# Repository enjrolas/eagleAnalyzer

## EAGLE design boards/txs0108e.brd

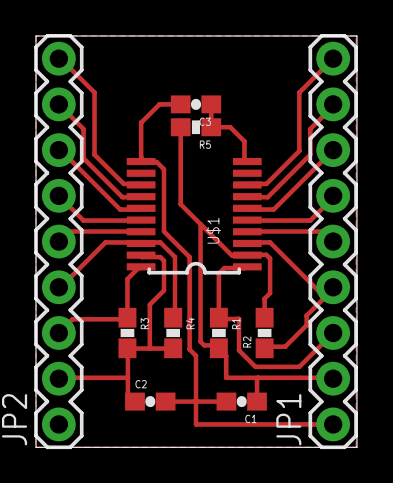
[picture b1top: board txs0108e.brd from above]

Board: 2 copper layers, 17.8 x 22.9 mm, 11 parts (0 on the bottom side), 18 nets.

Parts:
C1, C2, C3: 1uF; 0603-CAP
JP1, JP2: M09; 1X09
R1, R2, R3, R4: 4k7; 0603-RES
R5: 10k; 0603-RES
U$1: TXS0108E; TSSOP20

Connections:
3.3V: C1.1, JP1.2, R1.2, R2.2, R5.2, U$1.2
5V: C2.1, JP2.2, R3.2, R4.2, U$1.19
A1: JP1.3, R1.1, U$1.1
A2: JP1.4, R2.1, U$1.3
A3: JP1.5, U$1.4
A4: JP1.6, U$1.5
A5: JP1.7, U$1.6
A6: JP1.8, U$1.7
A7: JP1.9, U$1.8
B1: JP2.3, R3.1, U$1.20
B2: JP2.4, R4.1, U$1.18
B3: JP2.5, U$1.17
B4: JP2.6, U$1.16
B5: JP2.7, U$1.15
B6: JP2.8, U$1.14
B7: JP2.9, U$1.13
GND: C1.2, C2.2, C3.2, JP1.1, U$1.11
OE: C3.1, R5.1, U$1.10

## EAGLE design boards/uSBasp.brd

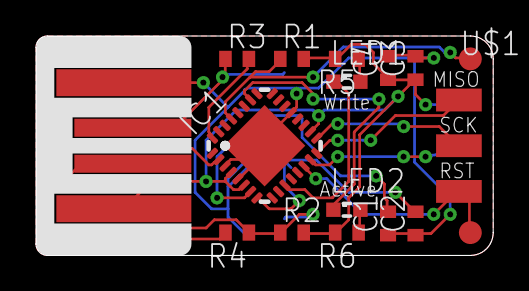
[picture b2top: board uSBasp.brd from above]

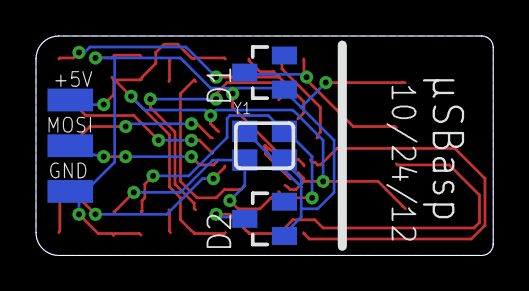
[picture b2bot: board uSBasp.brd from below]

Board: 2 copper layers, 25.4 x 12.2 mm, 20 parts (3 on the bottom side), 17 nets.

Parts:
C1, C2: 22pF; C0402
C3: 0.1uF; C0402
C4: 4.7uF; C0402
D1, D2: 3V6; SOT23
IC1: MEGA8-MI; MLF32-TH
LED1: Write (R); SML0603
LED2: Active (G); SML0603
R1: 10k; R0402
R2: 2.2k; R0402
R3, R4: 68; R0402
R5, R6: 1k; R0402
TP1, TP2: TEST-POINT3X5; PAD.03X.05
U$1: M-2X03PTH; M-2X03-0.1-PTH-EDGE
X1: USBPCB; USB-A-PCB
Y1: 12Mhz; CRYSTAL-SMD-3.2X2.5

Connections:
+5V: C3.1, C4.1, IC1.4, IC1.6, IC1.18, R1.2, R2.2, R5.2, R6.2, U$1.2, X1.5V
D+: IC1.32, R3.2
D-: IC1.2, R4.2
GND: C1.1, C2.1, C3.2, C4.2, D1.1, D2.1, IC1.3, IC1.5, IC1.21, IC1.TH, U$1.6, X1.GND, Y1.2, Y1.4
LED-A: IC1.26, LED2.C
LED-W: IC1.11, LED1.C
MISO: IC1.16, U$1.1
MOSI: IC1.15, U$1.4
unnamed: LED1.A, R5.1
unnamed: LED2.A, R6.1
unnamed: D1.3, R3.1, X1.USB_P
unnamed: D2.3, R2.1, R4.1, X1.USB_M
unnamed: C1.2, IC1.7, Y1.3
unnamed: C2.2, IC1.8, Y1.1
RESET: IC1.14, TP2.P$1, U$1.5
SCK: IC1.17, U$1.3
SELFPROG: IC1.29, R1.1, TP1.P$1

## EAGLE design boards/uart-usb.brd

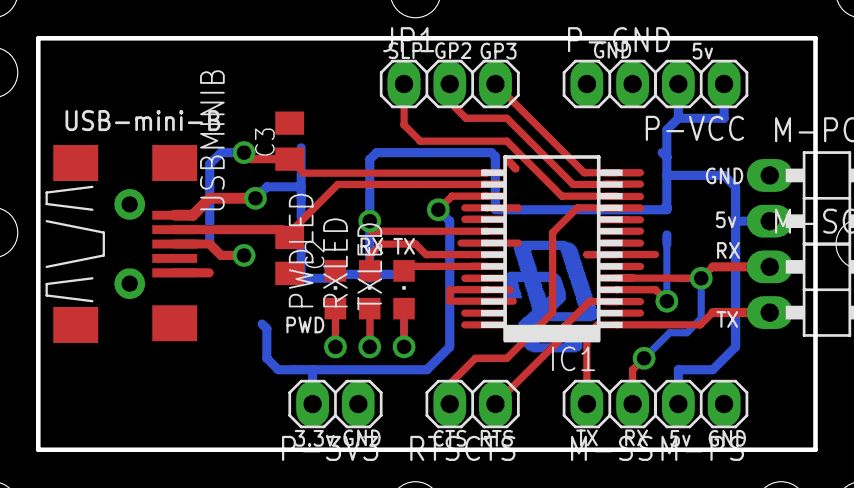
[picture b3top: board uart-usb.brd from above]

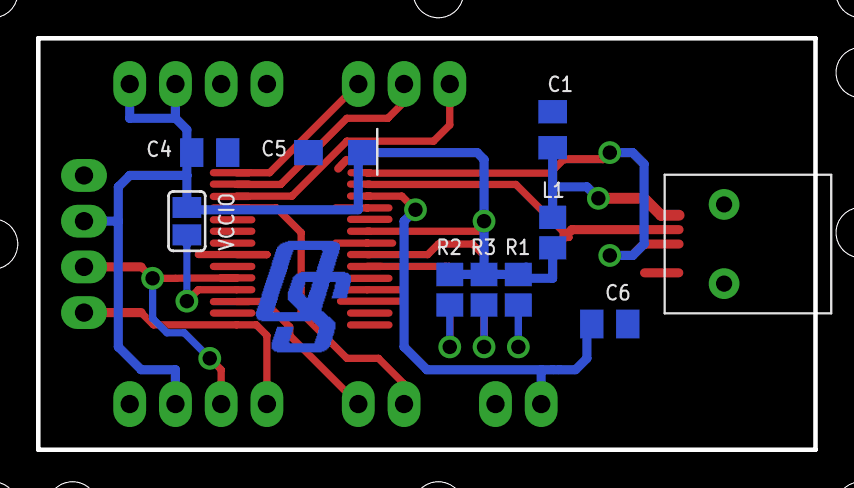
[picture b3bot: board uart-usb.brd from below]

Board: 2 copper layers, 43.2 x 22.9 mm, 27 parts (10 on the bottom side), 19 nets.

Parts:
C1: 10nF**; C0805K
C2, C3: 47pF**; C0805K
C4: 100nF; C0805K
C5: 4.7uF 20V; SMC_A
C6: 100n; C0805K
DRILEGEND: DRILEGEND
IC1: FT232RL; SSOP-28
JP1: 1X03
L1: 0 H; R0805
M-PC: 1X02/90
M-PS: 1X02
M-SC: 1X02/90
M-SS: 1X02
P-3V3: 1X02
P-GND: 1X02
P-VCC: 1X02
PWDLED: CHIPLED_0805
R1, R2: 270; R0805
R3: 510; R0805
RTSCTS: 1X02
RXLED: CHIPLED_0805
TXLED: CHIPLED_0805
U$1: SMP_OS12
USBMINIB: USB-MB-S
VCCIO: SJ

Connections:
3V3OUT: C6.1, IC1.17, P-3V3.2
CTS: IC1.11, RTSCTS.2
D+: C3.1, IC1.15, USBMINIB.D+
D-: C2.1, IC1.16, USBMINIB.D-
GND: C1.2, C2.2, C3.2, C4.2, C5.-, C6.2, IC1.7, IC1.18, IC1.21, IC1.25, IC1.26, M-PC.1, M-PS.1, P-3V3.1, P-GND.1, P-GND.2, PWDLED.C, USBMINIB.GND
GPIO2: IC1.13, JP1.2
GPIO3: IC1.14, JP1.3
unnamed: R3.2, RXLED.A
unnamed: PWDLED.A, R1.2
unnamed: R2.2, TXLED.A
unnamed: C1.1, L1.1, USBMINIB.VBUS
RTS: IC1.3, RTSCTS.1
RXD: IC1.5, M-SC.1, M-SS.1
RXLED: IC1.22, RXLED.C
SLEEP: IC1.12, JP1.1
TXD: IC1.1, M-SC.2, M-SS.2
TXLED: IC1.23, TXLED.C
VCC: C4.1, C5.+, IC1.20, L1.2, M-PC.2, M-PS.2, P-VCC.1, P-VCC.2, R1.1, R2.1, R3.1, VCCIO.1
VCCIO: IC1.4, VCCIO.2

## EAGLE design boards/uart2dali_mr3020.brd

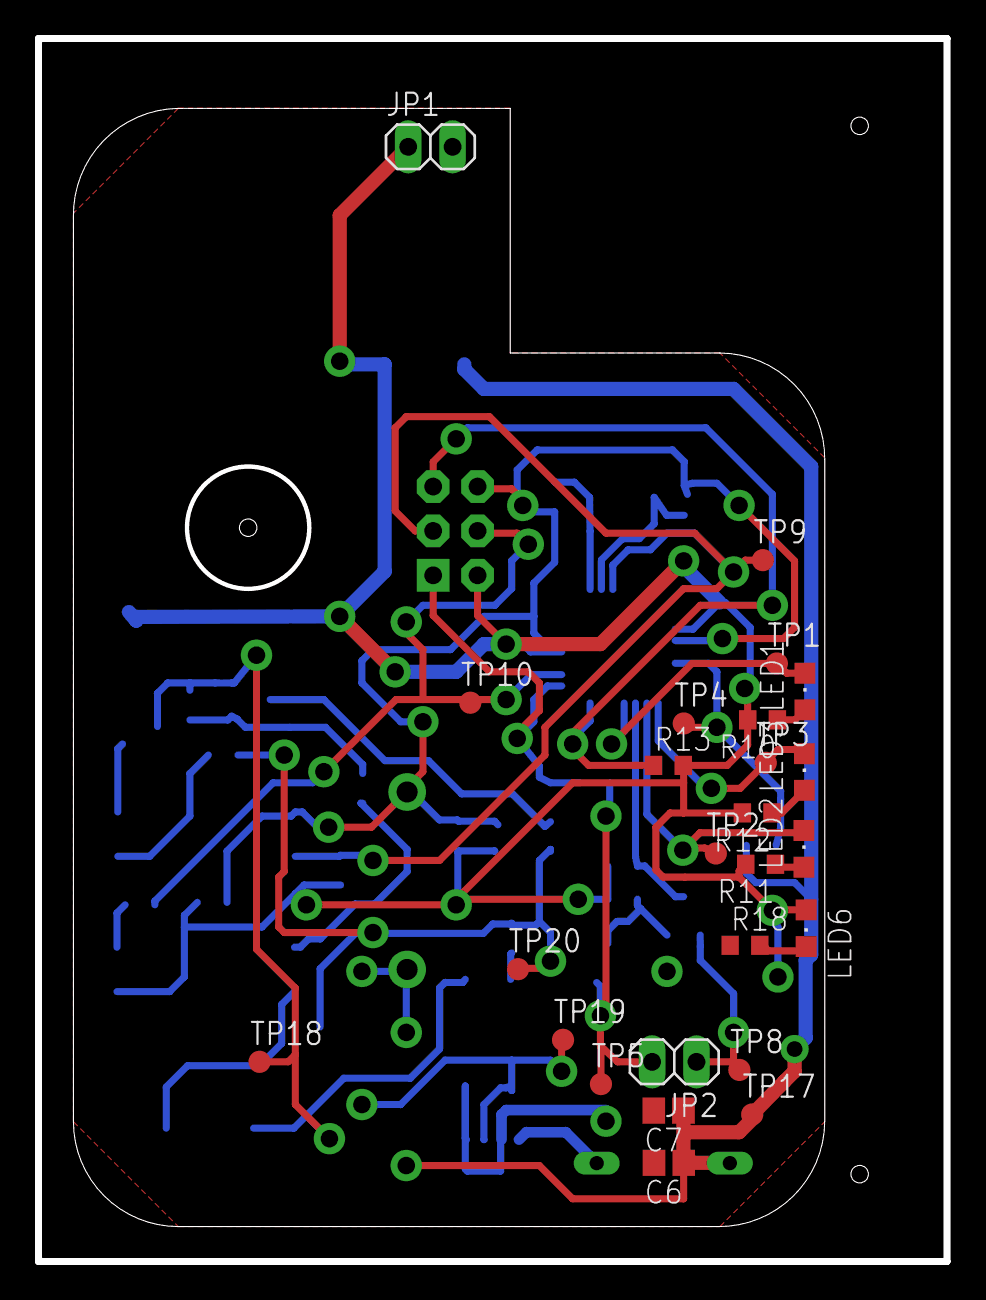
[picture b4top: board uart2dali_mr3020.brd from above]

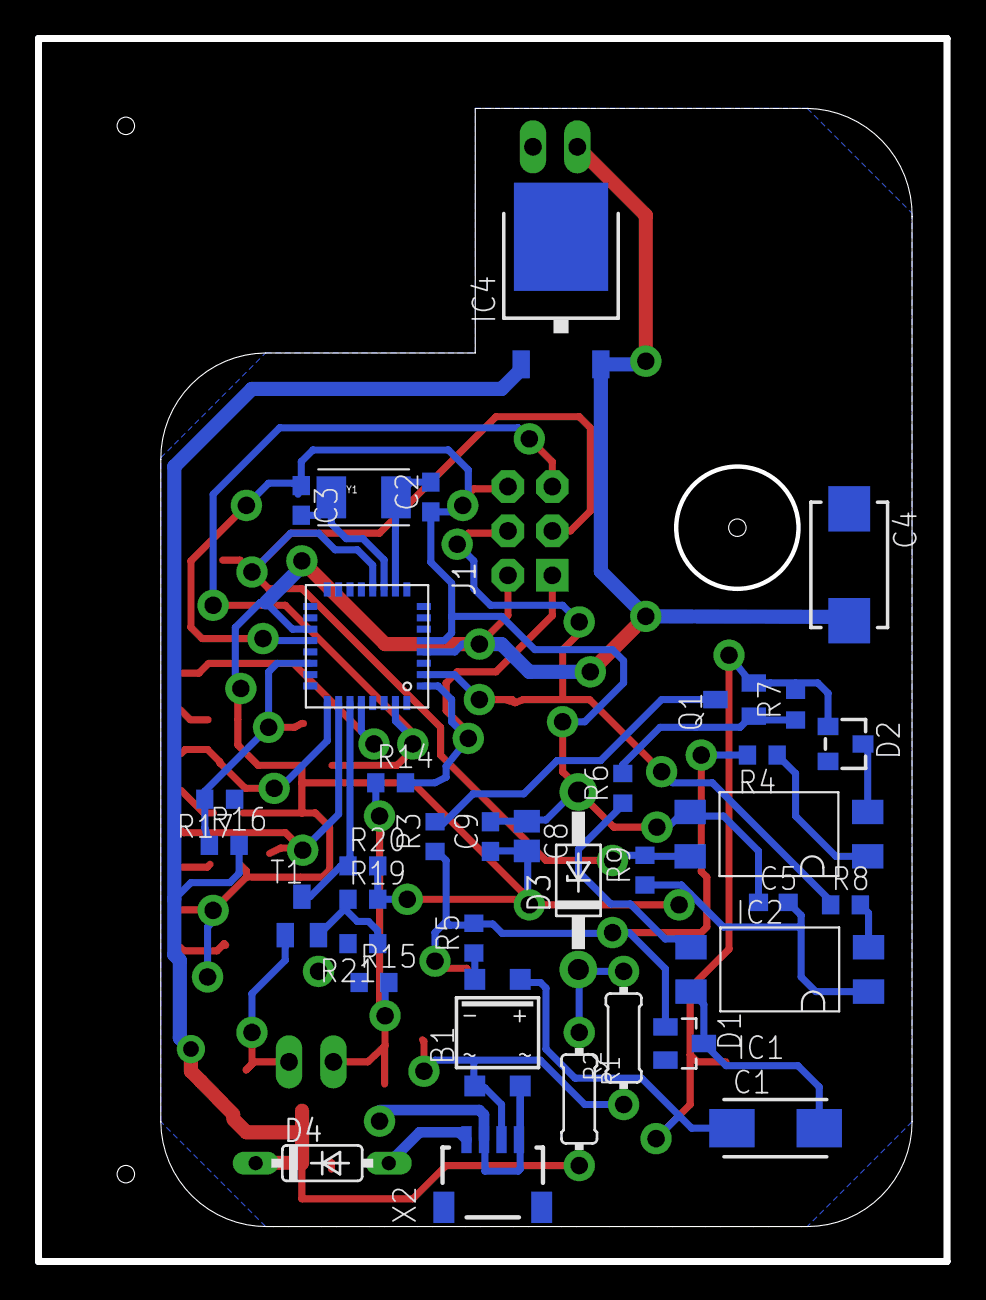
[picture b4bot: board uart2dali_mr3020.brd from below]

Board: 2 copper layers, 52.0 x 70.0 mm, 62 parts (37 on the bottom side), 34 nets.

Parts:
B1: MB2S; SOIC-4
C1: CT6032
C2, C3, C5, C9: C0603
C4: CT7343
C6, C7, C8: C0805
D1: BAS40; SOT23
D2: BZX84CSMD; TO236
D3: BZX85; DO41Z10
D4: 1N4148DO35-7; DO35-7
IC1, IC2: SFH6156; SFH
IC4: 7805DT; TO252
J1: AVR_SPI_PRG_6NS; 2X3-NS
JP1, JP2: 1X02
LED1, LED2, LED3, LED6: CHIPLED_0805
Q1: BC817-25SMD; SOT23-BEC
R1, R2: 0204/7
R3, R4, R5, R6, R7, R8, R9, R10, R11, R12, R13, R14, R15, R16, R17, R18, R19, R20, R21: R0603
T1: SOT23-EBC
TP1, TP2, TP3, TP4, TP5, TP8, TP9, TP10, TP17, TP18, TP19, TP20: TPB1,27; B1,27
U$1: AT90PWM316; QFN32_7MM
X2: SM04B-SRSS-TB
Y1: CRYSTAL-TXC-7A

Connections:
+5V: C4.+, C5.2, C8.2, C9.1, IC1.1, IC4.2, J1.2, JP1.1, LED6.A, R9.1, R10.2, R11.2, R12.2, R13.2, R19.2, R20.2, U$1.P4, U$1.P19
DALI_RCV: IC2.4, J1.3, R9.2, TP9.TP, U$1.P12
DALI_TRM: J1.4, R8.1, TP10.TP, U$1.P2
GND: B1.~2, C2.1, C3.1, C4.-, C5.1, C6.2, C7.2, C8.1, C9.2, D3.A, IC2.3, IC4.3, J1.6, JP1.2, R15.1, R17.1, R18.1, R21.2, U$1.P5, U$1.P20, X2.2, X2.4
MISO: J1.1, R14.2, U$1.P1
unnamed: IC1.2, R8.2
unnamed: B1.~1, R2.1, TP19.TP, X2.3
unnamed: D3.C, R1.1, R2.2
unnamed: C1.+, D1.3, IC1.4
unnamed: IC1.3, R6.1
unnamed: Q1.B, R6.2, R7.1
unnamed: B1.+, C1.-, D2.A, Q1.E, R7.2, TP18.TP
unnamed: LED1.A, R10.1
unnamed: D1.1, R3.1, R4.2, R5.2, TP20.TP
unnamed: Q1.C, R3.2
unnamed: IC2.1, R4.1
unnamed: D2.C, IC2.2
unnamed: B1.-, R5.1
unnamed: LED2.A, R11.1
unnamed: LED3.A, R12.1
unnamed: C2.2, U$1.P10, Y1.P$1
unnamed: C3.2, U$1.P11, Y1.P$2
unnamed: R19.1, R21.1, T1.B
unnamed: R20.1, T1.C, U$1.P27
unnamed: D4.A, X2.1
unnamed: LED3.C, TP3.TP, U$1.P25
unnamed: LED2.C, TP2.TP, U$1.P26
unnamed: LED1.C, TP1.TP, U$1.P28
unnamed: R16.1, R17.2, TP4.TP, U$1.P22
unnamed: LED6.C, R18.2
RESET: J1.5, R13.1, U$1.P31
SOFT_RXD: JP2.1, T1.E, TP8.TP
SOFT_TXD: JP2.2, R14.1, R15.2, TP5.TP
VDD: C6.1, C7.1, D4.C, IC4.1, R1.2, R16.2, TP17.TP

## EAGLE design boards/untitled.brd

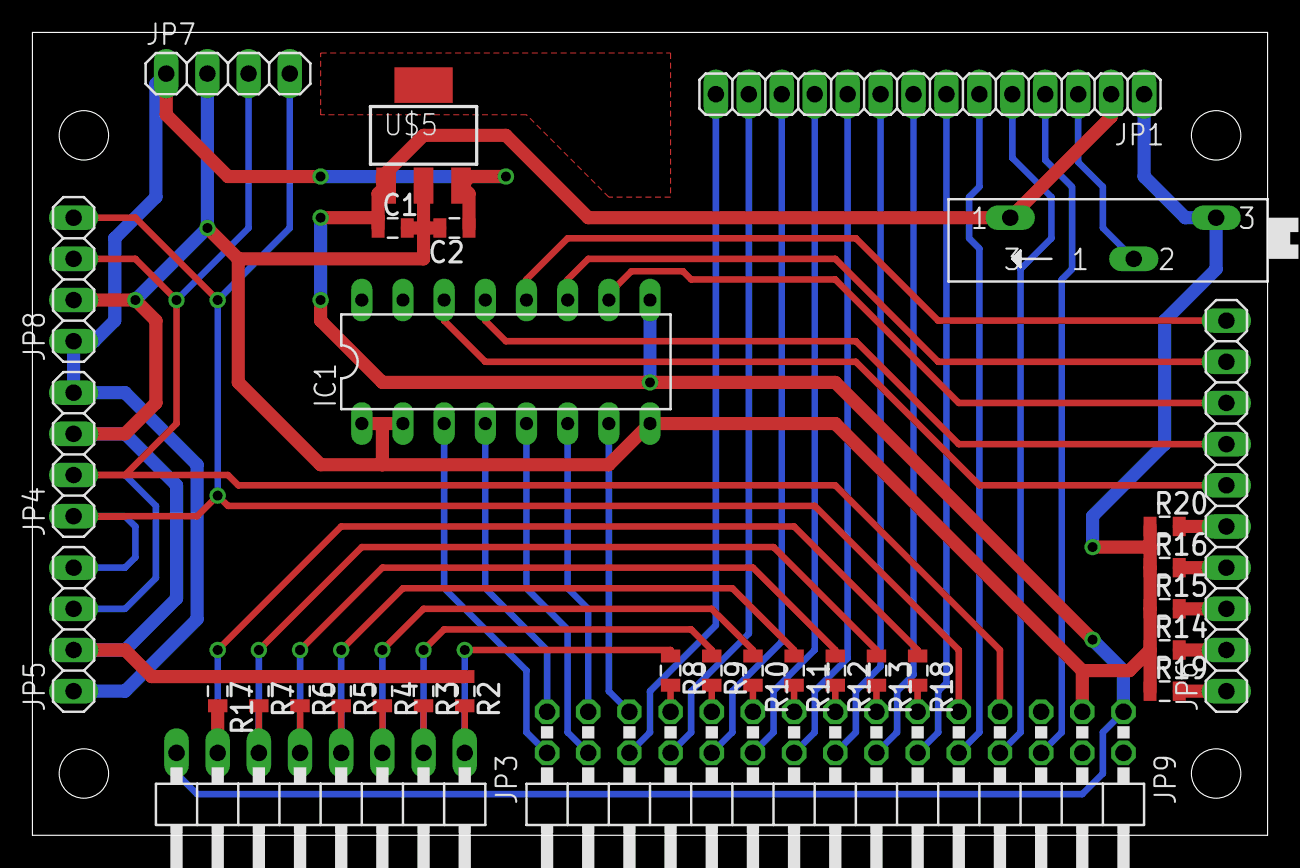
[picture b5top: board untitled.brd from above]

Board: 2 copper layers, 76.2 x 49.5 mm, 36 parts (0 on the bottom side), 46 nets.

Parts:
C1, C2: 0805
IC1: ULN2004AN; DIL16
JP1: 1X14
JP3: 1X08/90
JP4, JP5, JP7, JP8: 1X04
JP6: 1X10
JP9: 2X15/90
R1: SP19L
R2, R3, R4, R5, R6, R7, R8, R9, R10, R11, R12, R13, R14, R15, R16, R17, R18, R19, R20: 0805
U$1, U$2, U$3, U$4: STAND-OFF-TIGHT
U$5: LM3940IMP-3.3; SOT223

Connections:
3.3V: C2.1, JP4.4, JP5.1, JP7.1, JP8.1, U$5.3
GND: C1.2, C2.2, IC1.1, IC1.2, IC1.8, JP1.1, JP4.3, JP5.2, JP7.2, JP8.2, JP9.3, R1.E, R2.1, R3.1, R4.1, R5.1, R6.1, R7.1, R14.1, R15.1, R16.1, R17.1, R19.1, R20.1, U$5.2
unnamed: JP1.3, R1.S
unnamed: JP3.1, R2.2, R8.1
unnamed: JP3.2, R3.2, R9.1
unnamed: JP1.4, JP9.6
unnamed: JP1.5, JP9.8
unnamed: JP1.6, JP9.10
unnamed: JP1.7, JP9.12
unnamed: JP4.1, JP5.4, JP7.4, JP8.4, JP9.9
unnamed: JP1.8, JP9.14
unnamed: JP1.9, JP9.16
unnamed: JP1.10, JP9.18
unnamed: JP1.11, JP9.20
unnamed: JP1.12, JP9.22
unnamed: JP1.13, JP9.24
unnamed: JP3.3, R4.2, R10.1
unnamed: JP3.4, R5.2, R11.1
unnamed: JP3.5, R6.2, R12.1
unnamed: JP3.6, R7.2, R13.1
unnamed: JP9.13, R13.2
unnamed: JP9.15, R12.2
unnamed: JP9.17, R11.2
unnamed: JP9.19, R10.2
unnamed: JP9.21, R9.2
unnamed: JP9.23, R8.2
unnamed: JP1.14, JP9.26
unnamed: JP3.7, R17.2, R18.1
unnamed: IC1.7, JP9.25
unnamed: JP6.2, R14.2
unnamed: JP6.3, R15.2
unnamed: JP6.4, R16.2
unnamed: IC1.12, JP6.10
unnamed: IC1.5, JP9.28
unnamed: JP4.2, JP5.3, JP7.3, JP8.3, JP9.7
unnamed: JP9.11, R18.2
unnamed: JP6.1, R19.2
unnamed: JP6.5, R20.2
unnamed: IC1.4, JP9.29
unnamed: IC1.3, JP9.30
unnamed: IC1.10, JP6.8
unnamed: IC1.11, JP6.9
unnamed: IC1.13, JP6.7
unnamed: IC1.14, JP6.6
unnamed: IC1.6, JP9.27
VCC: C1.1, IC1.9, JP1.2, JP3.8, JP9.1, R1.A, U$5.1

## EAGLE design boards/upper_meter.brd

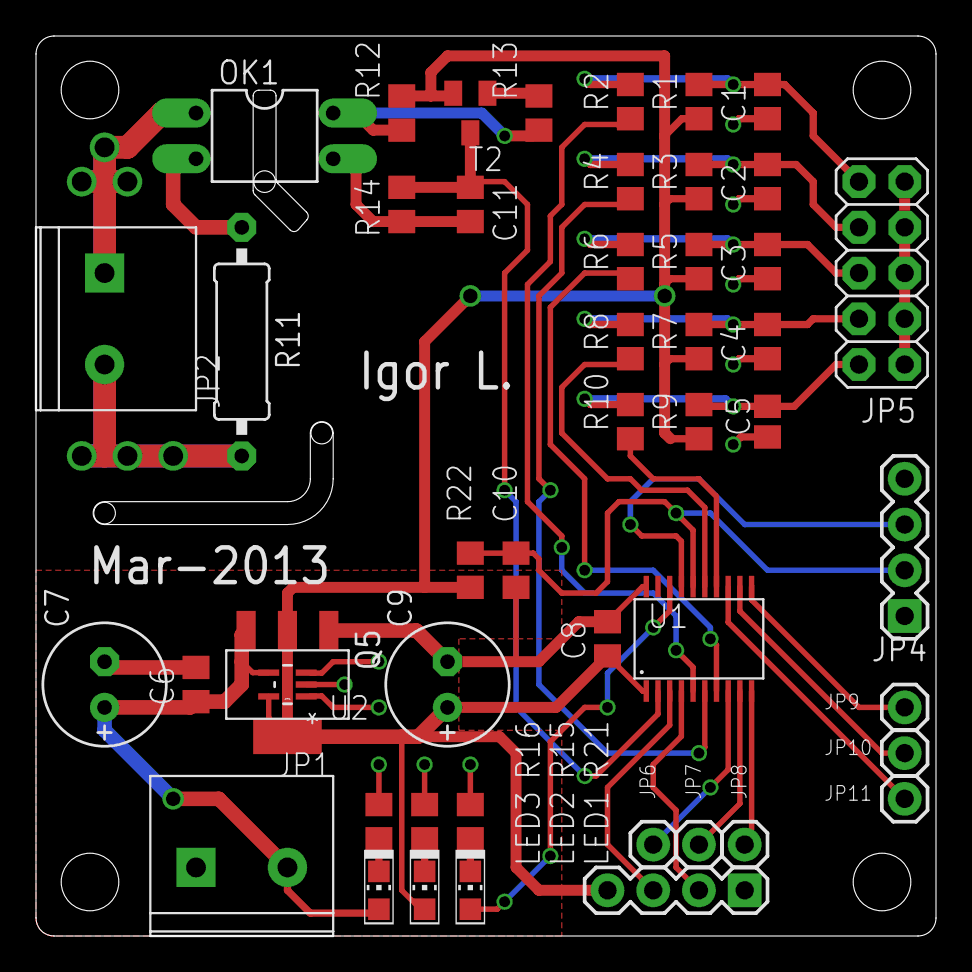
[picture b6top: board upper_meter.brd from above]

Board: 2 copper layers, 50.0 x 50.0 mm, 48 parts (0 on the bottom side), 33 nets.

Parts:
C1, C2, C3, C4, C5, C10, C11: 2.2nf; C0805
C6, C8: 0.47uF; C0805
C7, C9: 100 uF; E2,5-7
JP1: +5V; BLUE_TERM
JP2: ~220V; BLUE_TERM
JP3, JP4: 1X04
JP5: 2X05
JP6: P08; 1X01
JP7: P09; 1X01
JP8: P10; 1X01
JP9: P11; 1X01
JP10: P12; 1X01
JP11: P13; 1X01
LED1: BLUE; CHIP-LED0805
LED2: GREEN; CHIP-LED0805
LED3: RED; CHIP-LED0805
OK1: PC814; DIL04
Q5: TLV1117; SOT223-4
R1, R3, R5, R7, R9, R14: 4.7K; R0805
R2, R4, R6, R8, R10, R21: 470; R0805
R11: 200K 0.5W; 0309/12
R12: 10K; R0805
R13, R15, R16: 1K; R0805
R22: 47K; R0805
T2: MBT3906; SOT23-BEC
U1: G2XX3---PW20; PW20
U2: TPS71533_DCK_5; DCK5

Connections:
+3V3: C8.1, C9.+, JP3.4, LED2.A, Q5.2, Q5.4, R1.1, R3.1, R5.1, R7.1, R9.1, R12.2, R22.2, T2.E, U1.1, U2.5
+5V: C6.1, C7.+, JP1.2, LED3.A, Q5.3, U2.4
AC1: JP2.2, R11.1
AC2: JP2.1, OK1.1
GND: C1.1, C2.1, C3.1, C4.1, C5.1, C6.2, C7.-, C8.2, C9.-, C10.2, C11.2, JP1.1, JP3.1, JP4.1, JP5.2, JP5.4, JP5.6, JP5.8, JP5.10, OK1.3, Q5.1, R14.1, R15.1, R16.1, R21.1, U1.20, U2.2
LED: LED1.A, U1.18
unnamed: C2.2, JP5.3, R3.2, R4.2
unnamed: C1.2, JP5.1, R1.2, R2.2
unnamed: C3.2, JP5.5, R5.2, R6.2
unnamed: C4.2, JP5.7, R7.2, R8.2
unnamed: C5.2, JP5.9, R9.2, R10.2
unnamed: R13.2, T2.B
unnamed: LED2.C, R15.2
unnamed: LED3.C, R16.2
unnamed: OK1.4, R12.1, R13.1
unnamed: OK1.2, R11.2
unnamed: LED1.C, R21.2
P08: JP6.1, U1.8
P09: JP7.1, U1.9
P10: JP8.1, U1.10
P11: JP9.1, U1.11
P12: JP10.1, U1.12
P13: JP11.1, U1.13
RST: C10.1, JP4.2, R22.1, U1.16
RXD: JP3.3, U1.3
T1: R2.1, U1.5
T2: R4.1, U1.6
T3: R6.1, U1.7
T4: R8.1, U1.15
T5: R10.1, U1.14
TEST: JP4.3, U1.17
TXD: JP3.2, U1.4
ZC_DET: C11.1, R14.2, T2.C, U1.2

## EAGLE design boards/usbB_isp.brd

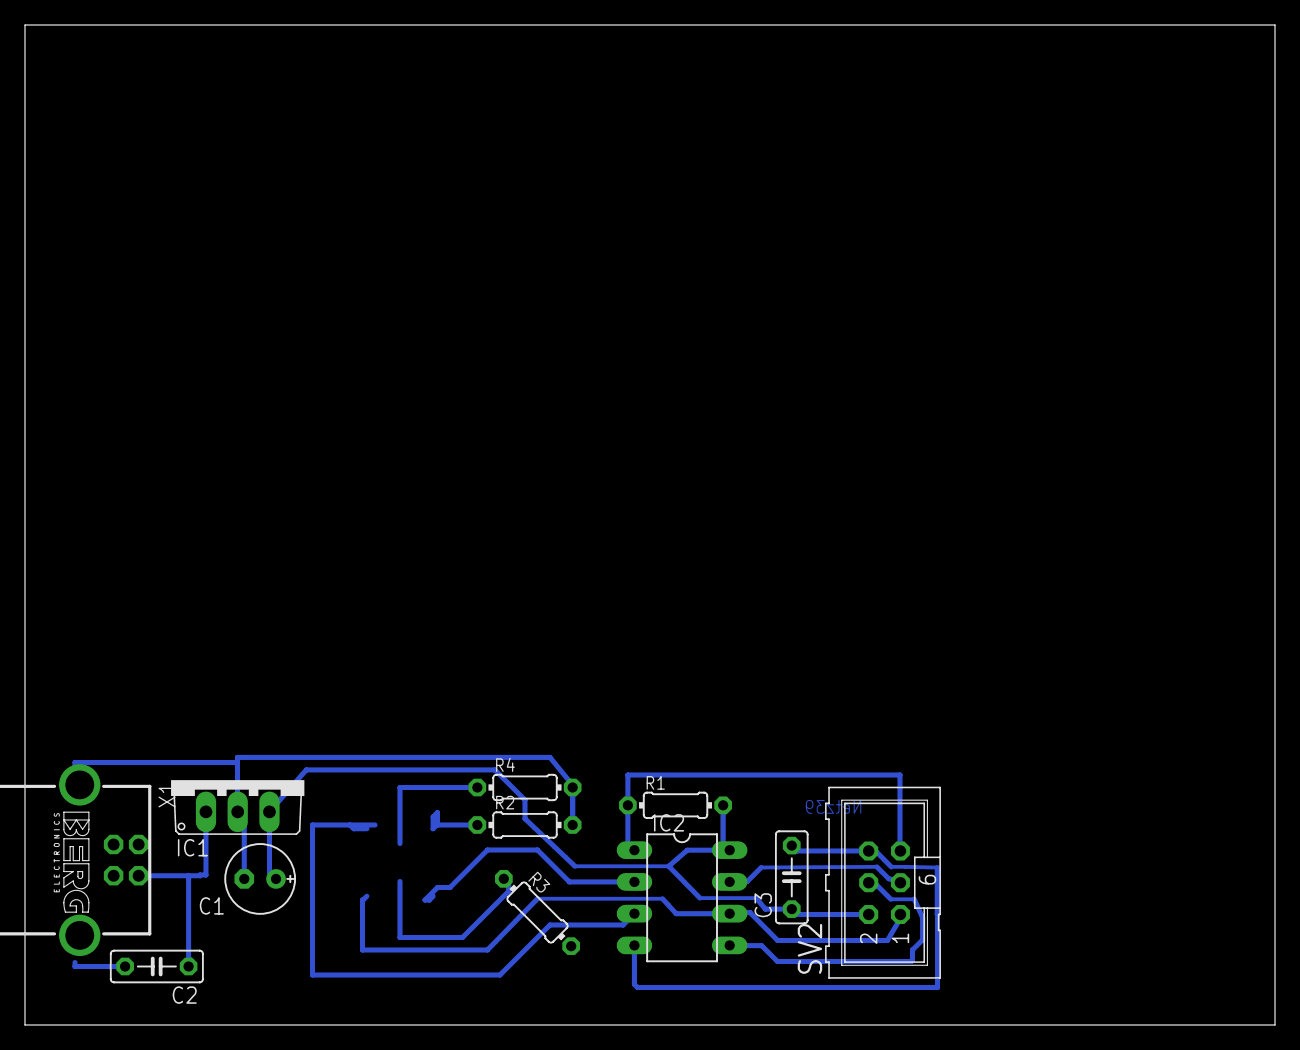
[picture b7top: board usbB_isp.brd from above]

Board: 2 copper layers, 100.0 x 80.0 mm, 12 parts (1 on the bottom side), 12 nets.

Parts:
C1: 33u; E2,5-6E
C2: 470n; C050-025X075
C3: 100n; C050-025X075
IC1: 788TV; TO220V
IC2: TINY13-20PU; DIL08
LED1: LRTB_G6SG
R1: 10k; 0204/7
R2: 150; 0204/7
R3, R4: 91; 0204/7
SV2: PROG; ML6
X1: PN61729-S

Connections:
GND: C1.-, C2.2, C3.2, IC1.2, IC2.4, R2.2, R3.2, R4.2, SV2.6, X1.S1
MISO: IC2.6, LED1.3, SV2.1
unnamed: C2.1, IC1.1, X1.1
unnamed: IC2.2, LED1.1
unnamed: LED1.5, R4.1
unnamed: LED1.2, R3.1
unnamed: LED1.6, R2.1
unnamed: IC2.3, LED1.4
unnamed: IC2.5, SV2.4
SCK: IC2.7, SV2.3
VCC: C1.+, C3.1, IC1.3, IC2.8, R1.2, SV2.2
_RESET: IC2.1, R1.1, SV2.5

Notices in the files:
parts and their libraries:
SparkFun-Connectors: Licensing: CC v3.0 Share-Alike You are welcome to use this library for commercial purposes.
